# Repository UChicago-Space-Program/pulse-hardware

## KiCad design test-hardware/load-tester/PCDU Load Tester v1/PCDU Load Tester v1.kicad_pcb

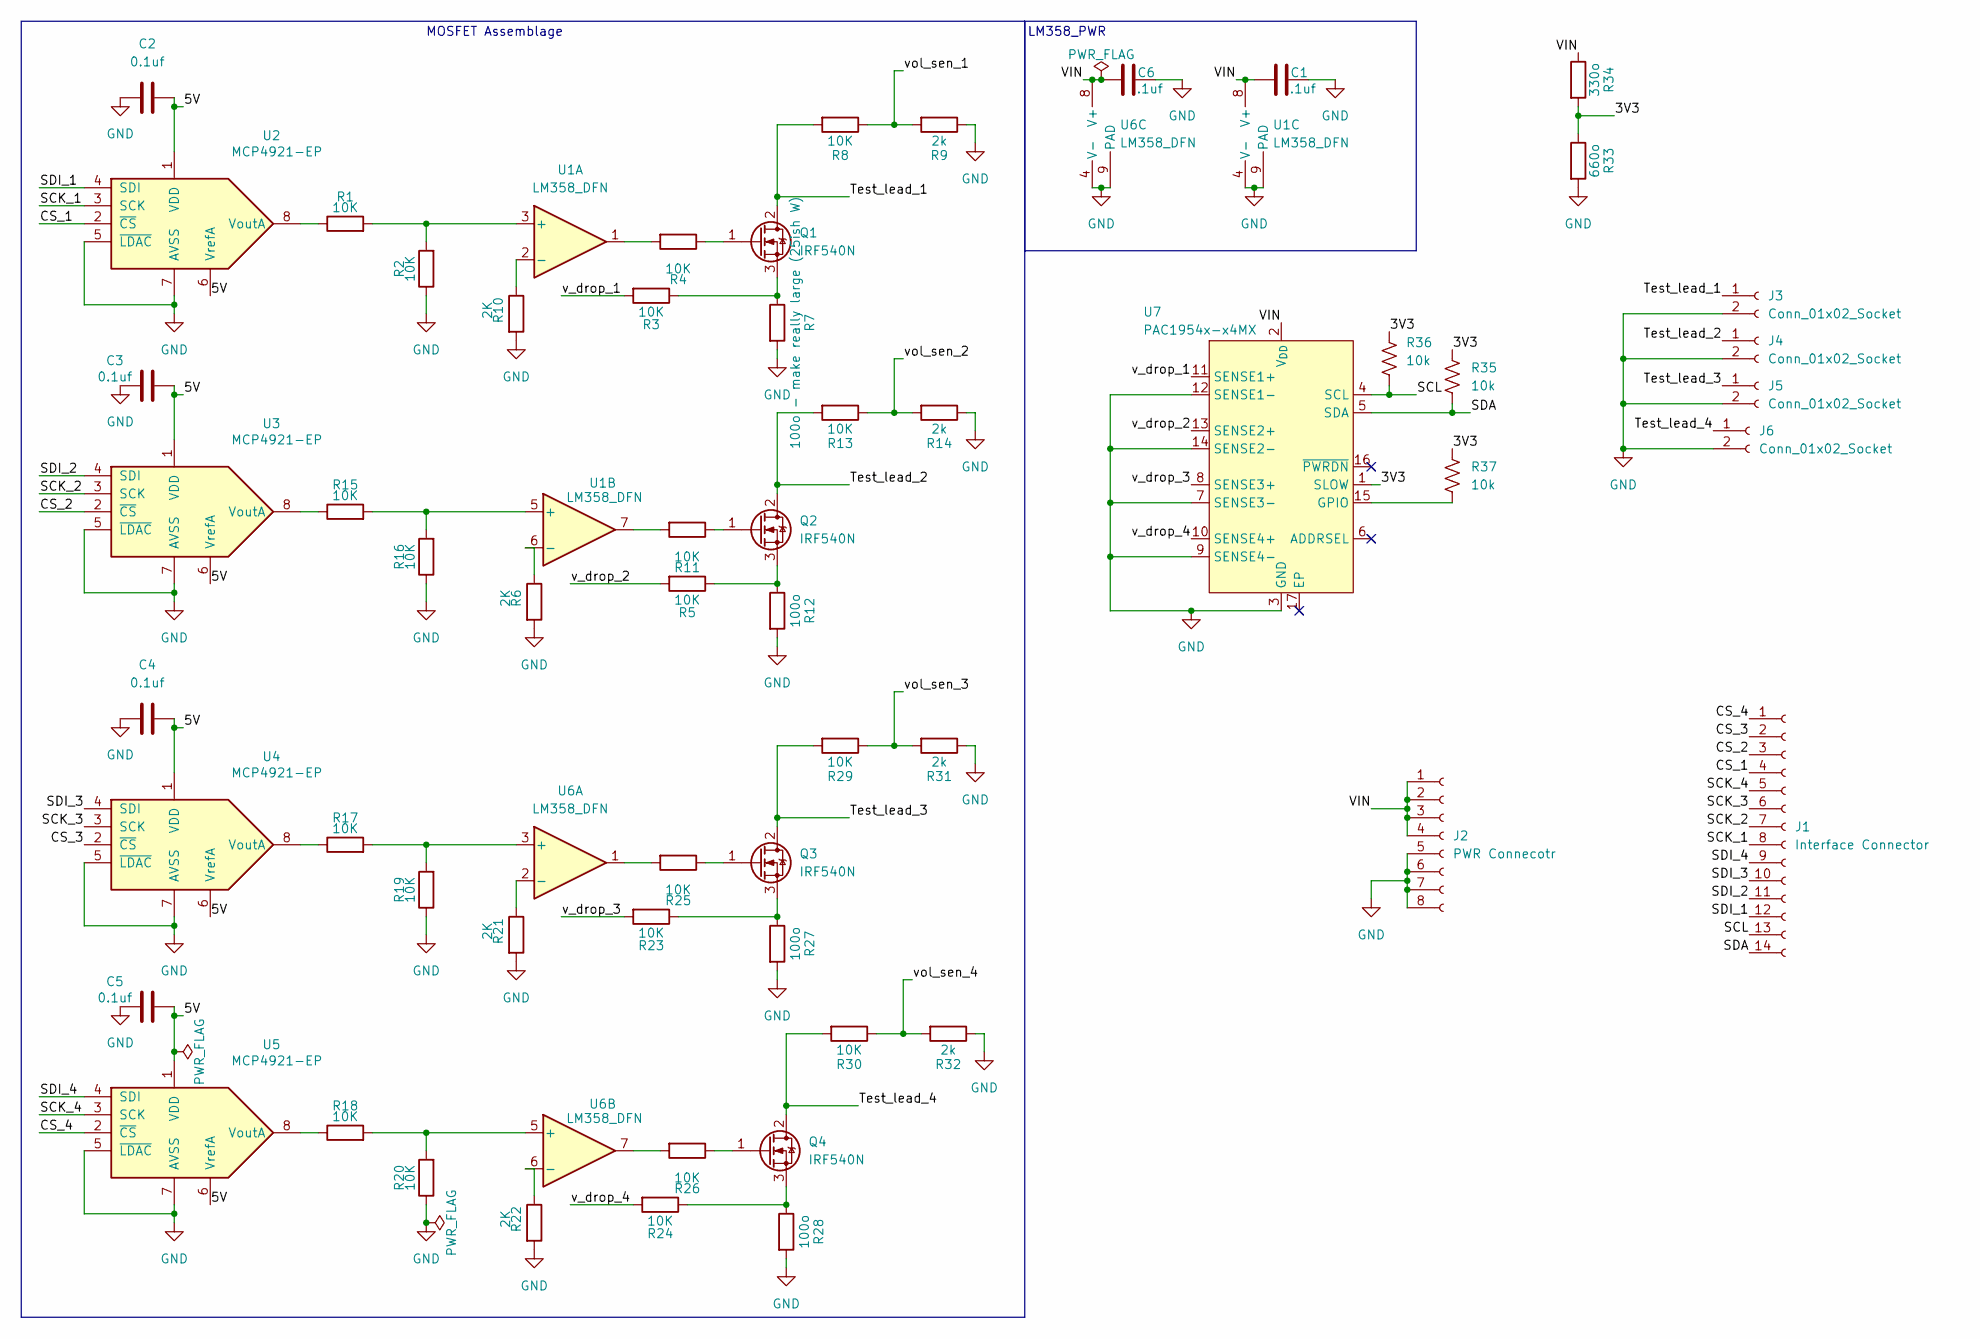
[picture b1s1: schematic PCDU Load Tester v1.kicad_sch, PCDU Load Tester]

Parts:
C1, C6: .1uf; C_0805_2012Metric
C2, C3, C4, C5: 0.1uf; C_0805_2012Metric
J1: Interface Connector; PinHeader_2x07_P2.54mm_Horizontal
J2: PWR Connecotr; PinHeader_2x04_P2.54mm_Horizontal
J3, J4, J5, J6: Conn_01x02_Socket; PinHeader_1x02_P2.54mm_Horizontal
Q1, Q2, Q3, Q4: IRF540N; TO-220-3_Vertical
R1, R2, R3, R4, R5, R8, R11, R13, R15, R16, R17, R18, R19, R20, R23, R24, R25, R26, R29, R30: 10K; R_0815_2038Metric
R6, R10, R21, R22: 2K; R_0815_2038Metric
R7: 100o - make really large (25ish W); R_0815_2038Metric
R9, R14, R31, R32: 2k; R_0815_2038Metric
R12, R27, R28: 100o; R_0815_2038Metric
R33: 660o; R_0815_2038Metric
R34: 330o; R_0815_2038Metric
R35, R36, R37: 10k; R_0815_2038Metric
U1, U6: LM358_DFN; DFN-8-1EP_2x2mm_P0.5mm_EP1.05x1.75mm
U2, U3, U4, U5: MCP4921-EP; DIP-8_W7.62mm
U7: PAC1954x-x4MX; VQFN-16-1EP_3x3mm_P0.5mm_EP1.1x1.1mm

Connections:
/3V3: R33.1, R34.2, R35.1, R36.1, R37.1, U7.1 (SLOW)
/5V: C2.1, C3.1, C4.1, C5.1, U2.1 (VDD), U2.6 (VrefA), U3.1 (VDD), U3.6 (VrefA), U4.1 (VDD), U4.6 (VrefA), U5.1 (VDD), U5.6 (VrefA)
/CS_1: J1.4, U2.2 (~CS)
/CS_2: J1.3, U3.2 (~CS)
/CS_3: J1.2, U4.2 (~CS)
/CS_4: J1.1, U5.2 (~CS)
/SCK_1: J1.8, U2.3 (SCK)
/SCK_2: J1.7, U3.3 (SCK)
/SCK_3: J1.6, U4.3 (SCK)
/SCK_4: J1.5, U5.3 (SCK)
/SCL: J1.13, R36.2, U7.4 (SCL)
/SDA: J1.14, R35.2, U7.5 (SDA)
/SDI_1: J1.12, U2.4 (SDI)
/SDI_2: J1.11, U3.4 (SDI)
/SDI_3: J1.10, U4.4 (SDI)
/SDI_4: J1.9, U5.4 (SDI)
/Test_lead_1: J3.1, Q1.2 (D), R8.2
/Test_lead_2: J4.1, Q2.2 (D), R13.2
/Test_lead_3: J5.1, Q3.2 (D), R29.2
/Test_lead_4: J6.1, Q4.2 (D), R30.2
/VIN: C1.1, C6.1, J2.1, J2.2, J2.3, J2.4, R34.1, U1.8 (V+), U6.8 (V+), U7.2 (V_{DD})
/v_drop_1: R3.2, U7.11 (SENSE1+)
/v_drop_2: R5.2, U7.13 (SENSE2+)
/v_drop_3: R23.2, U7.8 (SENSE3+)
/v_drop_4: R24.2, U7.10 (SENSE4+)
/vol_sen_1: R8.1, R9.2
/vol_sen_2: R13.1, R14.2
/vol_sen_3: R29.1, R31.2
/vol_sen_4: R30.1, R32.2
GND: C1.2, C2.2, C3.2, C4.2, C5.2, C6.2, J2.5, J2.6, J2.7, J2.8, J3.2, J4.2, J5.2, J6.2, R2.1, R6.2, R7.2, R9.1, R10.2, R12.2, R14.1, R16.1, R19.1, R20.1, R21.2, R22.2, R27.2, R28.2, R31.1, R32.1, R33.2, U1.4 (V-), U1.9 (PAD), U2.5 (~LDAC), U2.7 (AVSS), U3.5 (~LDAC), U3.7 (AVSS), U4.5 (~LDAC), U4.7 (AVSS), U5.5 (~LDAC), U5.7 (AVSS), U6.4 (V-), U6.9 (PAD), U7.3 (GND), U7.7 (SENSE3-), U7.9 (SENSE4-), U7.12 (SENSE1-), U7.14 (SENSE2-)
unnamed: Q1.1 (G), R4.1
unnamed: Q1.3 (S), R3.1, R7.1
unnamed: Q2.1 (G), R11.1
unnamed: Q2.3 (S), R5.1, R12.1
unnamed: Q3.1 (G), R25.1
unnamed: Q3.3 (S), R23.1, R27.1
unnamed: Q4.1 (G), R26.1
unnamed: Q4.3 (S), R24.1, R28.1
unnamed: R4.2, U1.1
unnamed: R11.2, U1.7
unnamed: R25.2, U6.1
unnamed: R26.2, U6.7
unnamed: R1.2, R2.2, U1.3 (+)
unnamed: R10.1, U1.2 (-)
unnamed: R15.2, R16.2, U1.5 (+)
unnamed: R6.1, U1.6 (-)
unnamed: R1.1, U2.8 (VoutA)
unnamed: R15.1, U3.8 (VoutA)
unnamed: R17.1, U4.8 (VoutA)
unnamed: R18.1, U5.8 (VoutA)
unnamed: R17.2, R19.2, U6.3 (+)
unnamed: R21.1, U6.2 (-)
unnamed: R18.2, R20.2, U6.5 (+)
unnamed: R22.1, U6.6 (-)
unnamed: R37.2, U7.15 (GPIO)

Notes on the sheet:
LM358_PWR
MOSFET Assemblage

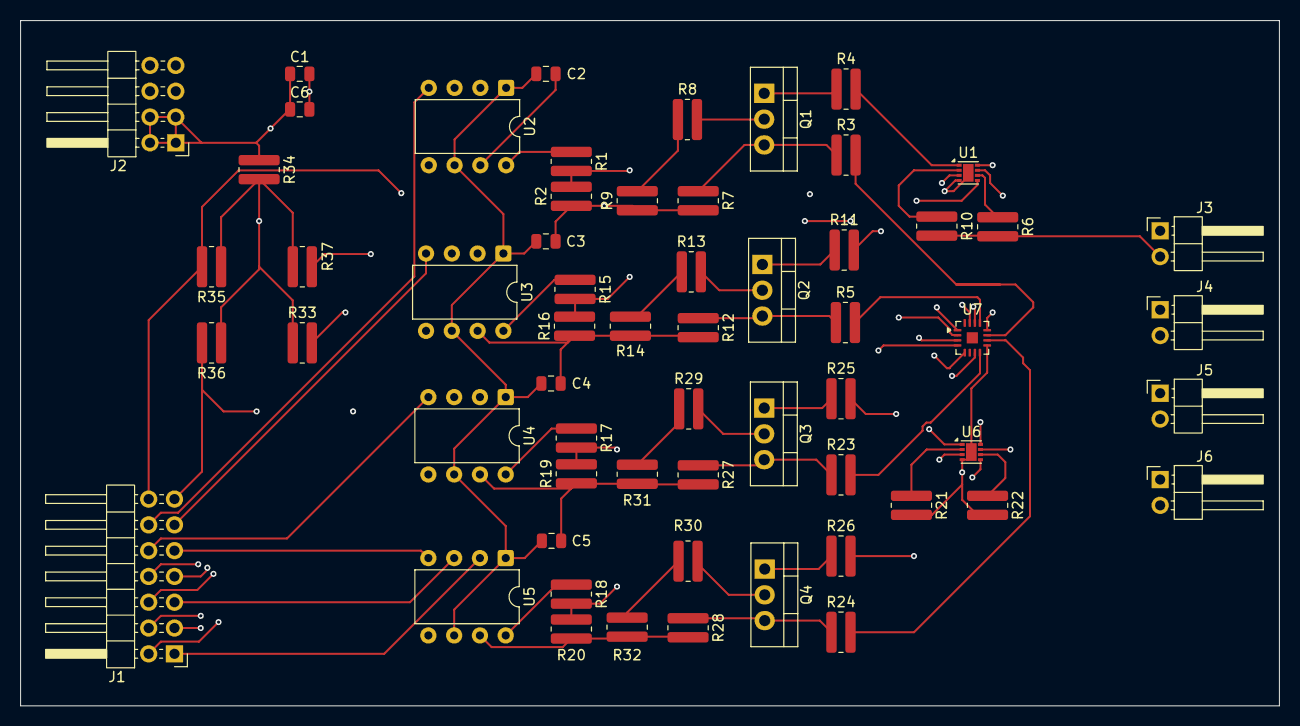
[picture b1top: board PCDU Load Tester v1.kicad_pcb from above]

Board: 4 copper layers, 124.0 x 67.5 mm, 60 parts (0 on the bottom side), 55 nets.

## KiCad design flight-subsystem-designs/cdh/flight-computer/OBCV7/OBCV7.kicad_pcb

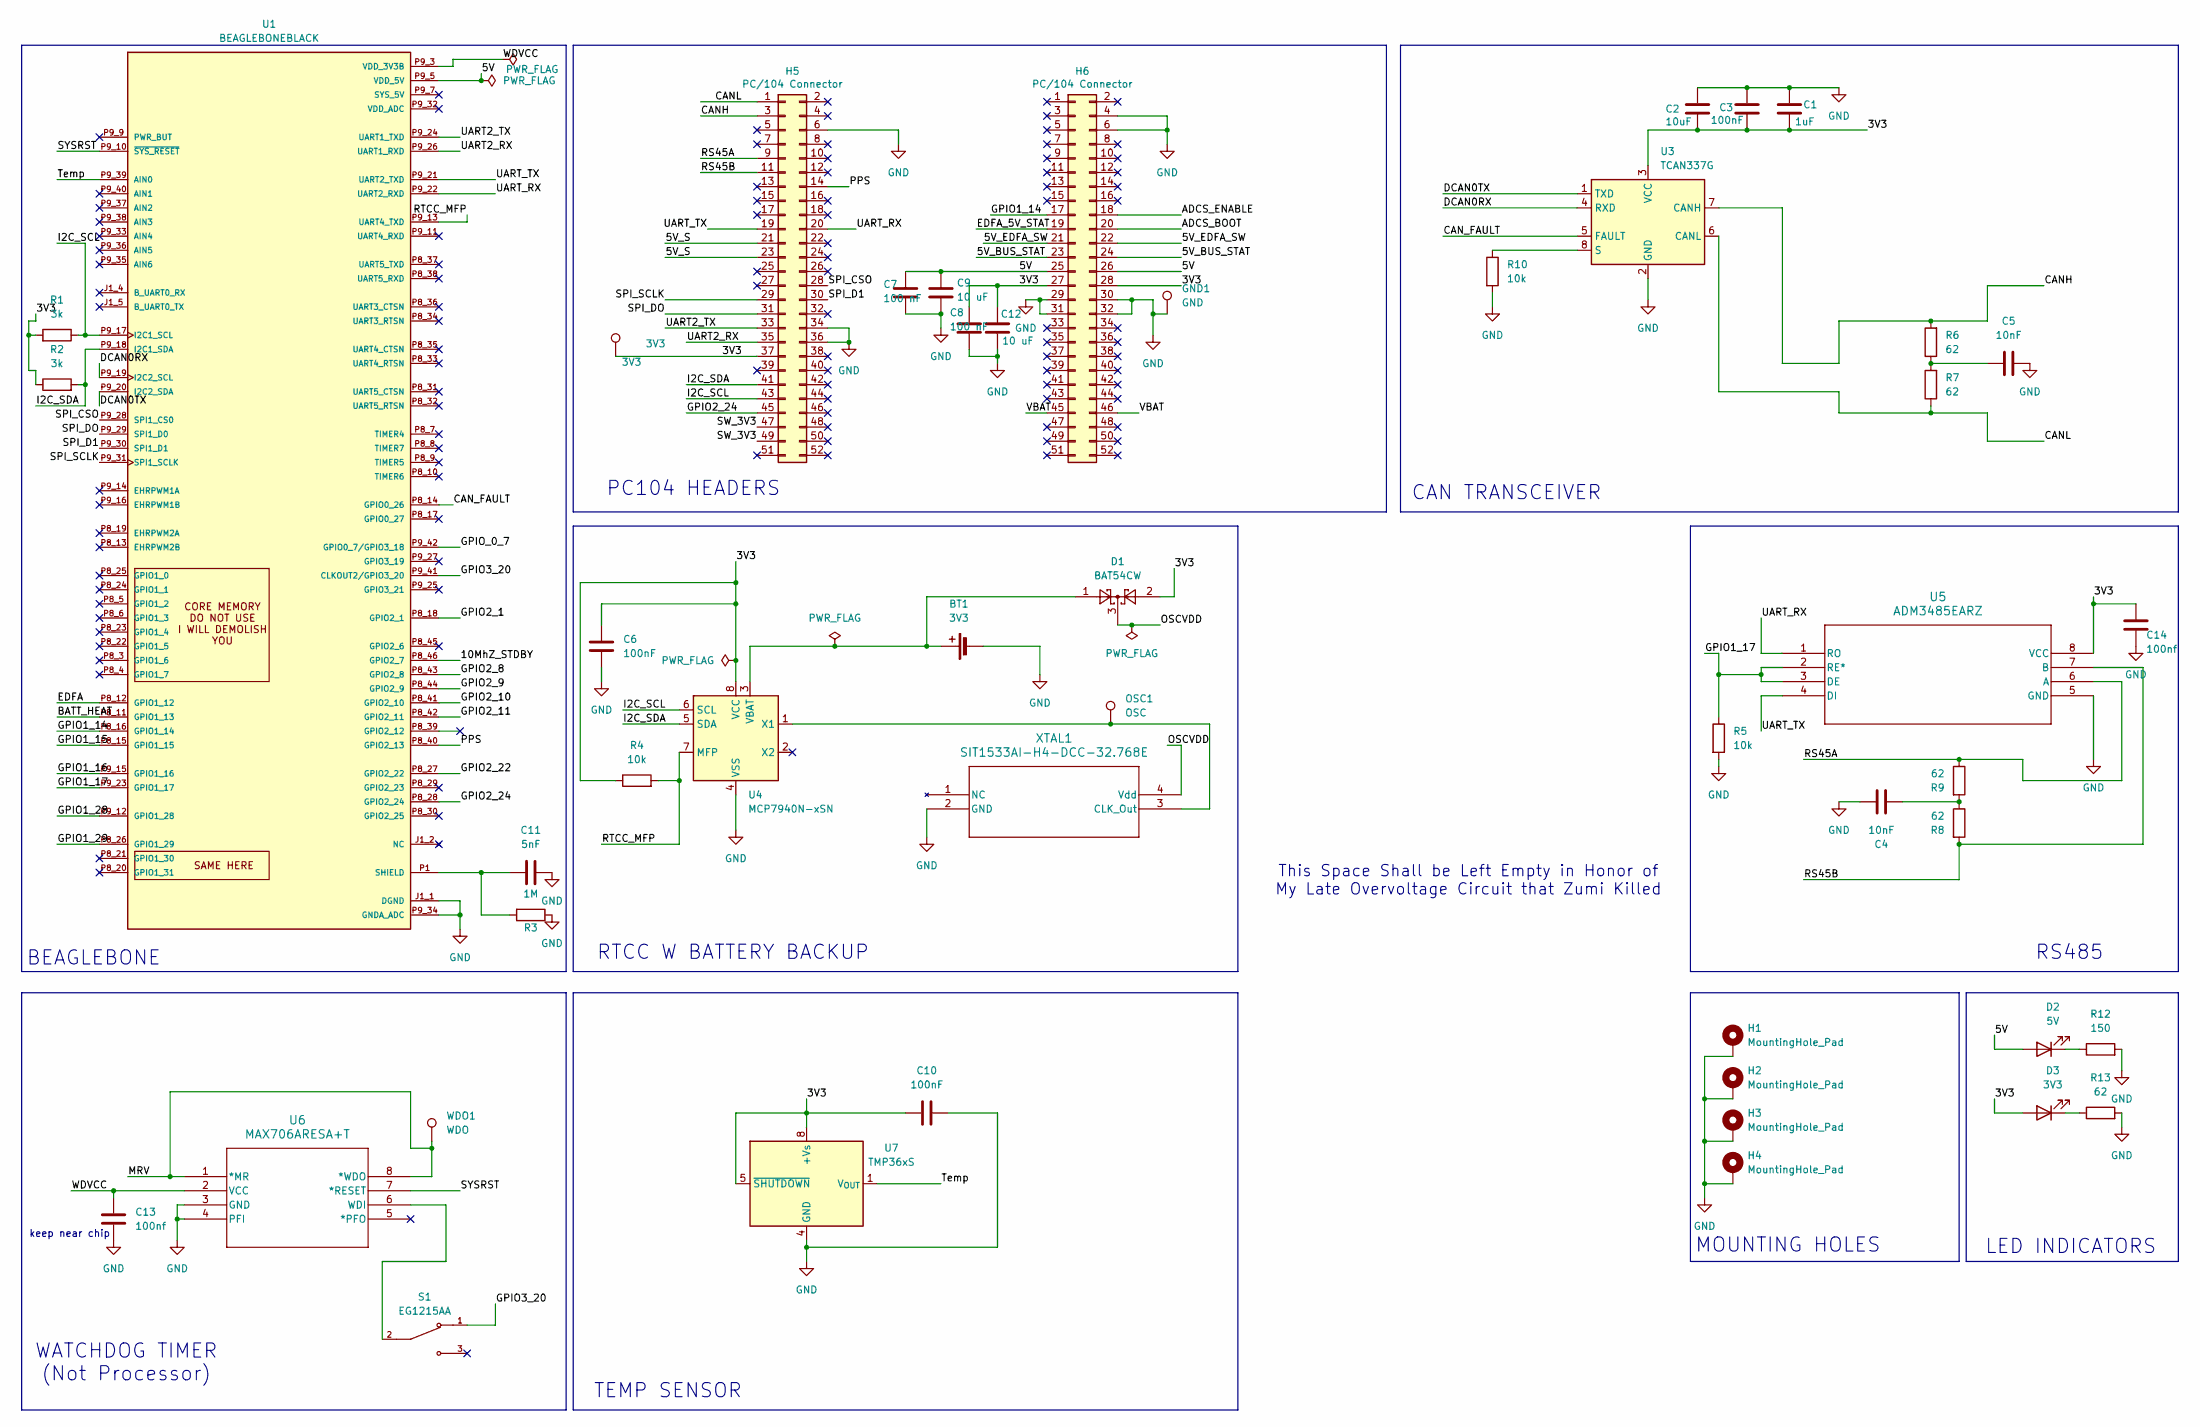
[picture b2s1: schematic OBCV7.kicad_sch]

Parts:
3V3: 3V3; TestPoint_THTPad_D3.0mm_Drill1.5mm
BT1: 3V3; BatteryHolder_Keystone_106_1x20mm
C1: 1uF; C_0805_2012Metric_Pad1.18x1.45mm_HandSolder
C2: 10uF; C_0805_2012Metric_Pad1.18x1.45mm_HandSolder
C3, C6, C10: 100nF; C_0805_2012Metric_Pad1.18x1.45mm_HandSolder
C4, C5: 10nF; C_0805_2012Metric_Pad1.18x1.45mm_HandSolder
C7, C8: 100 nF; C_0805_2012Metric_Pad1.18x1.45mm_HandSolder
C9, C12: 10 uF; C_0805_2012Metric_Pad1.18x1.45mm_HandSolder
C11: 5nF; C_0805_2012Metric_Pad1.18x1.45mm_HandSolder
C13, C14: 100nf; C_0805_2012Metric_Pad1.18x1.45mm_HandSolder
D1: BAT54CW; SOT-323_SC-70
D2: 5V; LED_0805_2012Metric
D3: 3V3; LED_0805_2012Metric
GND1: GND; TestPoint_THTPad_D3.0mm_Drill1.5mm
H1, H2, H3, H4: MountingHole_Pad; MountingHole_3.2mm_M3_Pad_TopBottom
H5, H6: PC/104 Connector; PinSocket_2x26_P2.54mm_Vertical
OSC1: OSC; TestPoint_THTPad_D3.0mm_Drill1.5mm
R1, R2: 3k; R_0805_2012Metric_Pad1.20x1.40mm_HandSolder
R3: 1M; R_0805_2012Metric_Pad1.20x1.40mm_HandSolder
R4, R5, R10: 10k; R_0805_2012Metric_Pad1.20x1.40mm_HandSolder
R6, R7, R8, R9: 62; R_0805_2012Metric_Pad1.20x1.40mm_HandSolder
R12: 150; LED_0805_2012Metric
R13: 62; LED_0805_2012Metric
S1: EG1215AA; SW_EG1215AA; PARTREV A
U1: BEAGLEBONEBLACK; MODULE_BEAGLEBONEBLACK; PARTREV C
U3: TCAN337G; TCAN337GD
U4: MCP7940N-xSN; SOIC8-N_MC_MCH
U5: ADM3485EARZ; R_8_ADI
U6: MAX706ARESA+T; 21-0041B_8_MXM
U7: TMP36xS; SOIC-8_3.9x4.9mm_P1.27mm
WDO1: WDO; TestPoint_THTPad_D3.0mm_Drill1.5mm
XTAL1: SIT1533AI-H4-DCC-32.768E; XTAL4_SiT1533_SIT

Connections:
/3V3: 3V3.1, C1.1, C2.2, C3.1, C6.1, C8.1, C10.1, C12.1, C14.2, D1.2, D3.2 (A), H5.37, H6.27, H6.28, R1.2, R2.1, R4.1, U3.3 (VCC), U4.8 (VCC), U5.8 (VCC), U7.5 (~SHUTDOWN), U7.8 (+Vs)
/5V_BUS_STAT: H6.23, H6.24
/5V_EDFA_SW: H6.21, H6.22
/5V_S: H5.21, H5.23
/10MhZ_STDBY: U1.P8_46 (GPIO2_7)
/ADCS_BOOT: H6.20
/ADCS_ENABLE: H6.18
/BATT_HEAT: U1.P8_11 (GPIO1_13)
/CANH: H5.3, R6.2, U3.7 (CANH)
/CANL: H5.1, R7.1, U3.6 (CANL)
/CAN_FAULT: U1.P8_14 (GPIO0_26), U3.5 (FAULT)
/DCAN0RX: U1.P9_19 (I2C2_SCL), U3.4 (RXD)
/DCAN0TX: U1.P9_20 (I2C2_SDA), U3.1 (TXD)
/EDFA: U1.P8_12 (GPIO1_12)
/EDFA_5V_STAT: H6.19
/GPIO1_14: H6.17, U1.P8_16 (GPIO1_14)
/GPIO1_15: U1.P8_15 (GPIO1_15)
/GPIO1_16: U1.P9_15 (GPIO1_16)
/GPIO1_17: R5.1, U1.P9_23 (GPIO1_17), U5.2 (RE*), U5.3 (DE)
/GPIO1_28: U1.P9_12 (GPIO1_28)
/GPIO1_29: U1.P8_26 (GPIO1_29)
/GPIO2_1: U1.P8_18 (GPIO2_1)
/GPIO2_8: U1.P8_43 (GPIO2_8)
/GPIO2_9: U1.P8_44 (GPIO2_9)
/GPIO2_10: U1.P8_41 (GPIO2_10)
/GPIO2_11: U1.P8_42 (GPIO2_11)
/GPIO2_22: U1.P8_27 (GPIO2_22)
/GPIO2_24: H5.45, U1.P8_28 (GPIO2_24)
/GPIO3_20: S1.1, U1.P9_41 (CLKOUT2/GPIO3_20)
/GPIO_0_7: U1.P9_42 (GPIO0_7/GPIO3_18)
/I2C_SCL: H5.43, R1.1, U1.P9_17 (I2C1_SCL), U4.6 (SCL)
/I2C_SDA: H5.41, R2.2, U1.P9_18 (I2C1_SDA), U4.5 (SDA)
/MRV: U6.1 (*MR), U6.8 (*WDO), WDO1.1
/OSCVDD: D1.3, XTAL1.4 (Vdd)
/PPS: H5.14, U1.P8_40 (GPIO2_13)
/RS45A: H5.9, R9.1, U5.6 (A)
/RS45B: H5.11, R8.2, U5.7 (B)
/RTCC_MFP: R4.2, U1.P9_13 (UART4_TXD), U4.7 (MFP)
/SPI_CSO: H5.28, U1.P9_28 (SPI1_CS0)
/SPI_D1: H5.30, U1.P9_30 (SPI1_D1)
/SPI_DO: H5.31, U1.P9_29 (SPI1_D0)
/SPI_SCLK: H5.29, U1.P9_31 (SPI1_SCLK)
/SW_3V3: H5.47, H5.49
/SYSRST: U1.P9_10 (~SYS_RESET), U6.7 (*RESET)
/Temp: U1.P9_39 (AIN0), U7.1 (V_{OUT})
/UART2_RX: H5.35, U1.P9_26 (UART1_RXD)
/UART2_TX: H5.33, U1.P9_24 (UART1_TXD)
/UART_RX: H5.20, U1.P9_22 (UART2_RXD), U5.1 (RO)
/UART_TX: H5.19, U1.P9_21 (UART2_TXD), U5.4 (DI)
/VBAT: H6.45, H6.46
GND: BT1.2 (-), C1.2, C2.1, C3.2, C4.2, C5.2, C6.2, C7.2, C8.2, C9.2, C10.2, C11.2, C12.2, C13.1, C14.1, GND1.1, H1.1, H2.1, H3.1, H4.1, H5.6, H5.34, H5.36, H6.4, H6.6, H6.29, H6.30, H6.31, H6.32, R3.1, R5.2, R10.2, R12.2, R13.2, U1.J1_1 (DGND), U1.P8_1 (DGND), U1.P8_2 (DGND), U1.P9_1 (DGND), U1.P9_2 (DGND), U1.P9_34 (GNDA_ADC), U1.P9_43 (DGND), U1.P9_44 (DGND), U1.P9_45 (DGND), U1.P9_46 (DGND), U3.2 (GND), U4.4 (VSS), U5.5 (GND), U6.3 (GND), U6.4 (PFI), U7.4 (GND), XTAL1.2 (GND)
unnamed: BT1.1 (+), D1.1, U4.3 (VBAT)
unnamed: C4.1, R8.1, R9.2
unnamed: C5.1, R6.1, R7.2
unnamed: C11.1, R3.2, U1.P1 (SHIELD), U1.P2 (SHIELD), U1.P3 (SHIELD), U1.P4 (SHIELD)
unnamed: D2.1 (K), R12.1
unnamed: D3.1 (K), R13.1
unnamed: R10.1, U3.8 (S)
unnamed: OSC1.1, U4.1 (X1), XTAL1.3 (CLK_Out)
unnamed: S1.2, U6.6 (WDI)
VDD_3V3B: C13.2, U1.P9_3 (VDD_3V3B), U1.P9_4 (VDD_3V3B), U6.2 (VCC)
VDD_5V: C7.1, C9.1, D2.2 (A), H6.25, H6.26, U1.P9_5 (VDD_5V), U1.P9_6 (VDD_5V)

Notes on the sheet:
RS485
TEMP SENSOR
This Space Shall be Left Empty in Honor of My Late Overvoltage Circuit that Zumi Killed
PC104 HEADERS
LED INDICATORS
CAN TRANSCEIVER
WATCHDOG TIMER (Not Processor)
RTCC W BATTERY BACKUP
MOUNTING HOLES
keep near chip
BEAGLEBONE

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
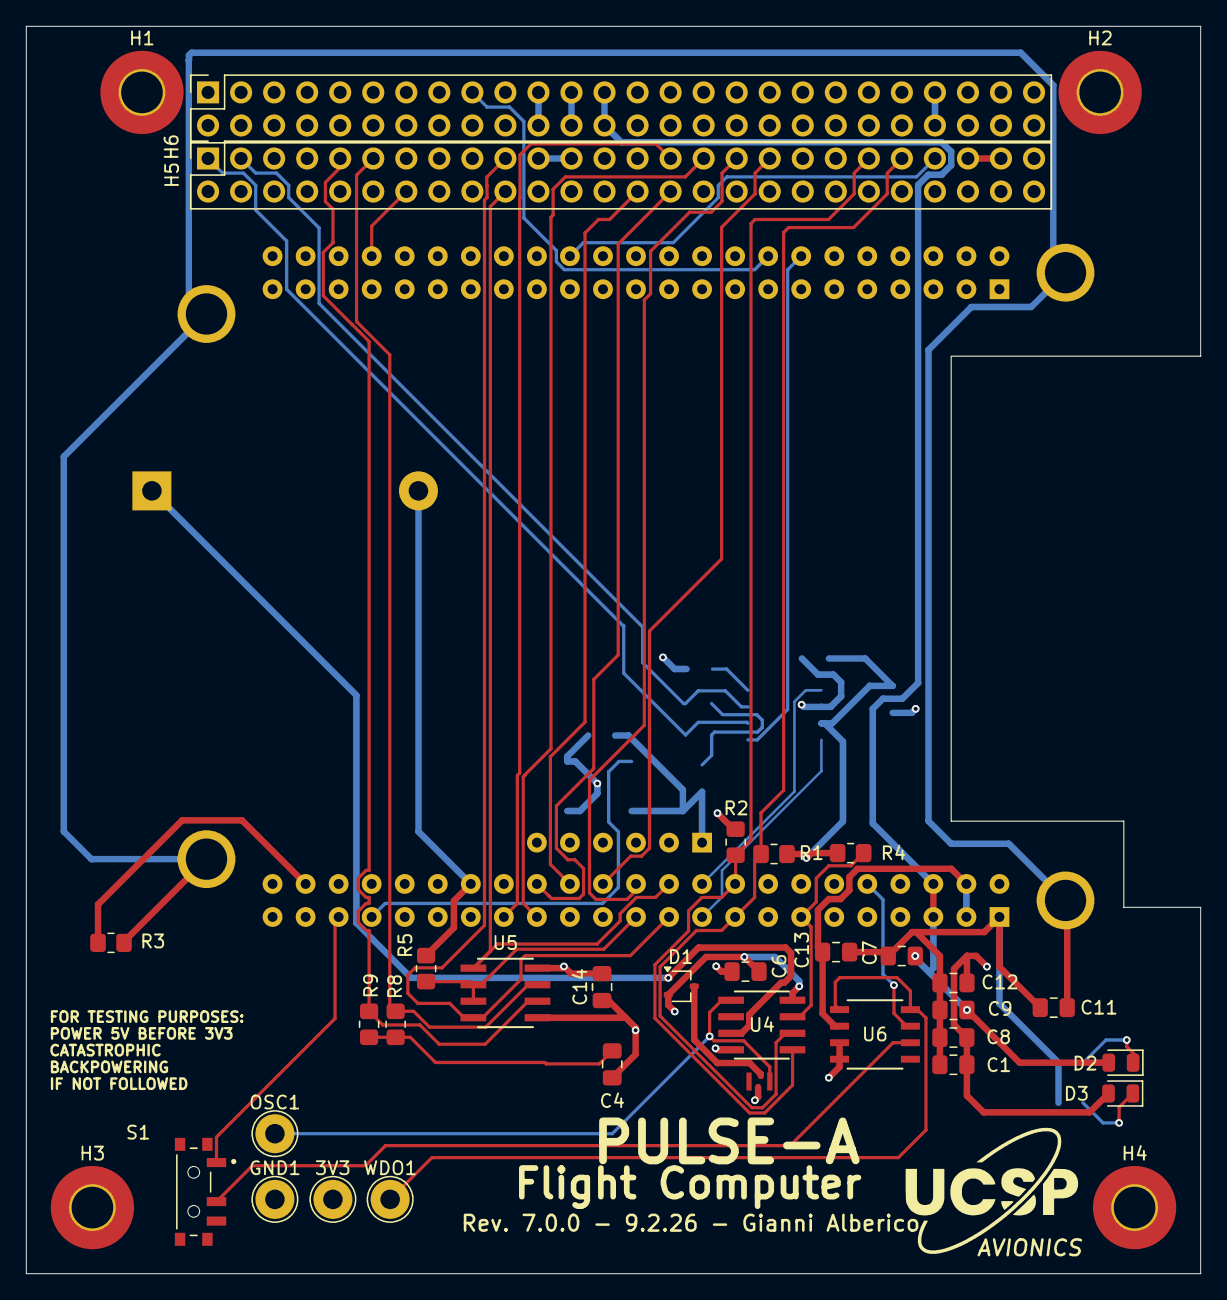
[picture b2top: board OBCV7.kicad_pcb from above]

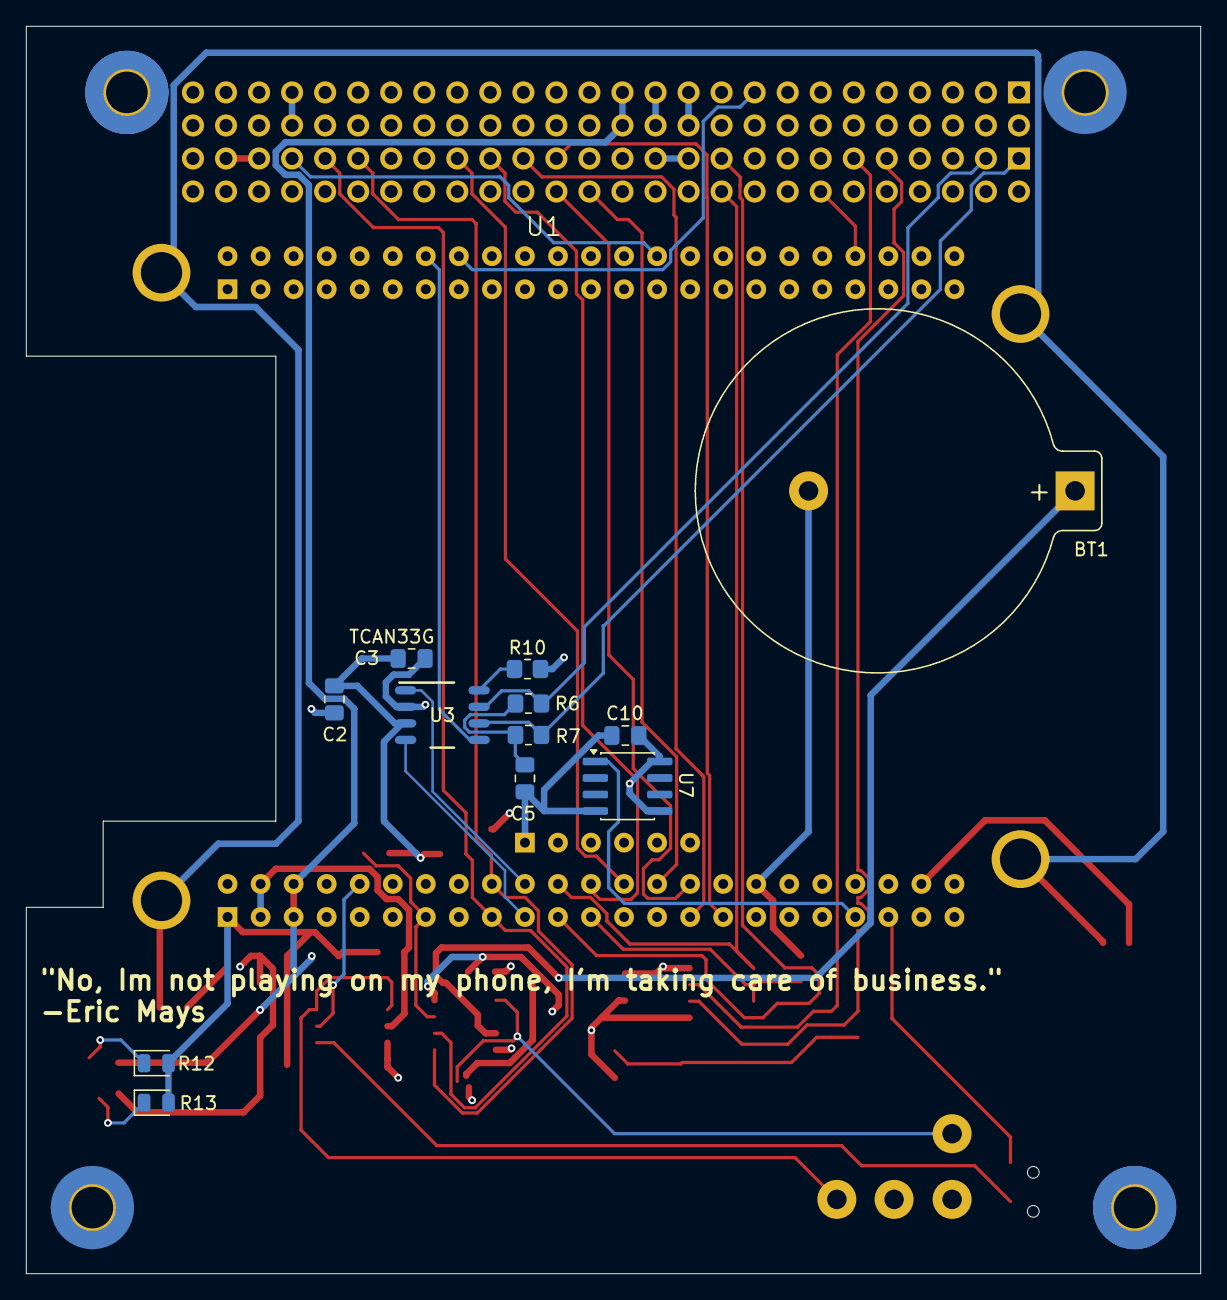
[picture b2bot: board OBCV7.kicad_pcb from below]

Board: 4 copper layers, 90.3 x 95.9 mm, 48 parts (13 on the bottom side), 45 nets.

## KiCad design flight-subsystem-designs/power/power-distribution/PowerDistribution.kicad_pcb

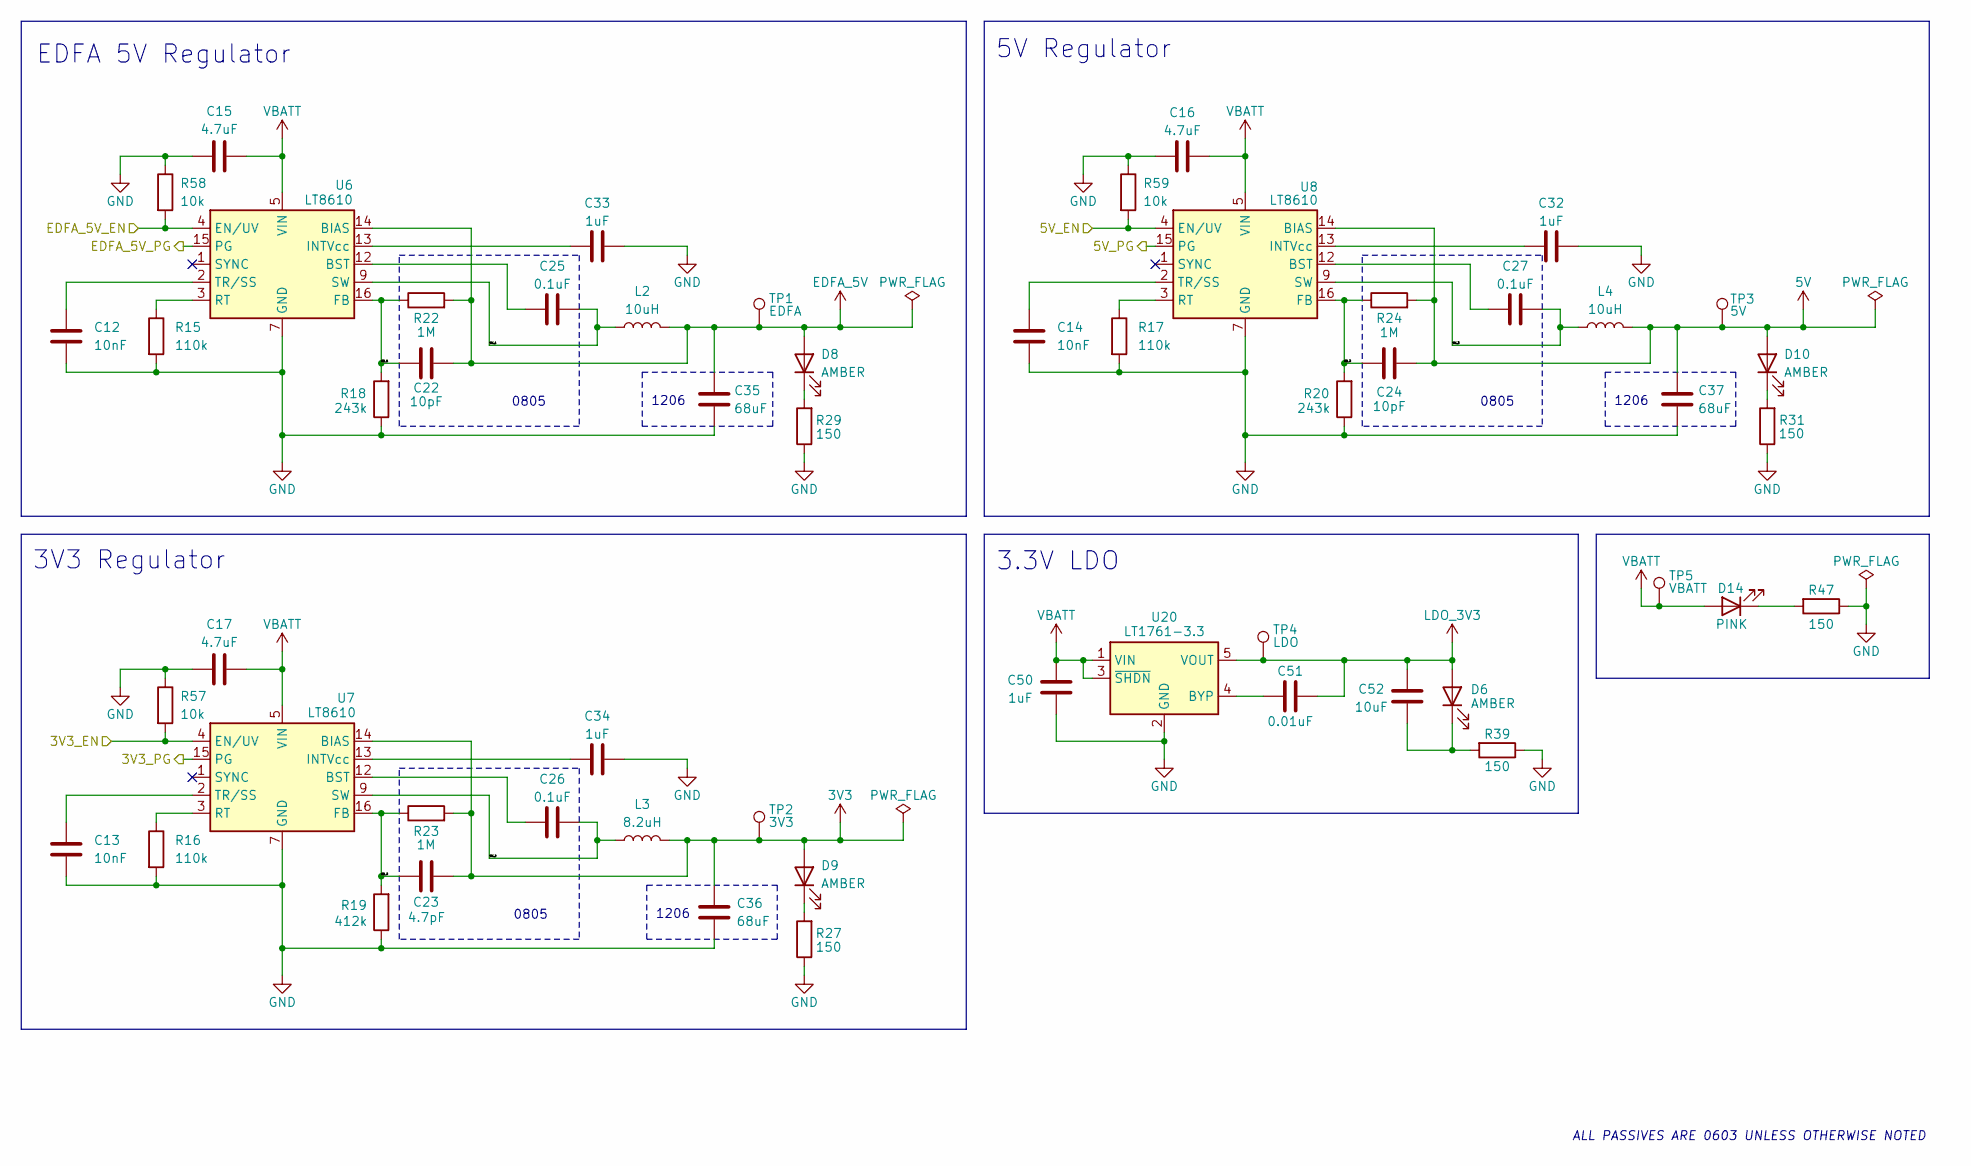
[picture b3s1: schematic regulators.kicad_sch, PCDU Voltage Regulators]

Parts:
C12, C13, C14: 10nF; C_0603_1608Metric
C15, C16, C17: 4.7uF; C_0603_1608Metric
C22, C24: 10pF; C_0805_2012Metric
C23: 4.7pF; C_0805_2012Metric
C25, C26, C27: 0.1uF; C_0805_2012Metric
C32, C33, C34, C50: 1uF; C_0603_1608Metric
C35, C36, C37: 68uF; C_1206_3216Metric
C51: 0.01uF; C_0603_1608Metric
C52: 10uF; C_0603_1608Metric
D6, D8, D9, D10: AMBER; LED_0603_1608Metric
D14: PINK; LED_0603_1608Metric
L2, L4: 10uH; L_Coilcraft_XxL4040
L3: 8.2uH; L_Coilcraft_XxL4040
R15, R16, R17: 110k; R_0603_1608Metric
R18, R20: 243k; R_0805_2012Metric
R19: 412k; R_0805_2012Metric
R22, R23, R24: 1M; R_0805_2012Metric
R27, R29, R31, R39, R47: 150; R_0603_1608Metric
R57, R58, R59: 10k; R_0603_1608Metric
TP1: EDFA; TestPoint_Keystone_5000-5004_Miniature
TP2: 3V3; TestPoint_Keystone_5000-5004_Miniature
TP3: 5V; TestPoint_Keystone_5000-5004_Miniature
TP4: LDO; TestPoint_Keystone_5000-5004_Miniature
TP5: VBATT; TestPoint_Keystone_5000-5004_Miniature
U6, U7, U8: LT8610; MSOP-16-1EP_3x4.039mm_P0.5mm_EP1.651x2.845mm_ThermalVias
U20: LT1761-3.3; TSOT-23-5

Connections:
3V3: C23.2, C36.2, D9.2 (A), L3.2, R23.2, TP2.1, U7.14 (BIAS); also elsewhere on the board
5V: C24.2, C37.2, D10.2 (A), L4.2, R24.2, TP3.1, U8.14 (BIAS); also elsewhere on the board
/Control/3V3_EN: R57.2, U7.4 (EN/UV); also elsewhere on the board
/Control/3V3_PG: U7.15 (PG); also elsewhere on the board
/Control/5V_EN: R59.2, U8.4 (EN/UV); also elsewhere on the board
/Control/5V_PG: U8.15 (PG); also elsewhere on the board
/Control/EDFA_5V_EN: R58.2, U6.4 (EN/UV); also elsewhere on the board
/Control/EDFA_5V_PG: U6.15 (PG); also elsewhere on the board
/Regulators/FB_1: C22.1, R18.2, R22.1, U6.16 (FB)
/Regulators/FB_2: C23.1, R19.2, R23.1, U7.16 (FB)
/Regulators/FB_3: C24.1, R20.2, R24.1, U8.16 (FB)
/Regulators/SW_1: C25.2, L2.1, U6.9 (SW), U6.10 (SW), U6.11 (SW)
/Regulators/SW_2: C26.2, L3.1, U7.9 (SW), U7.10 (SW), U7.11 (SW)
/Regulators/SW_3: C27.2, L4.1, U8.9 (SW), U8.10 (SW), U8.11 (SW)
EDFA_5V: C22.2, C35.2, D8.2 (A), L2.2, R22.2, TP1.1, U6.14 (BIAS); also elsewhere on the board
GND: C12.1, C13.1, C14.1, C15.1, C16.2, C17.1, C32.2, C33.2, C34.2, C35.1, C36.1, C37.1, C50.1, R15.2, R16.2, R17.2, R18.1, R19.1, R20.1, R27.1, R29.1, R31.1, R39.1, R47.1, R57.1, R58.1, R59.1, U6.7 (GND), U6.8 (GND), U6.17 (GND), U7.7 (GND), U7.8 (GND), U7.17 (GND), U8.7 (GND), U8.8 (GND), U8.17 (GND), U20.2 (GND); also elsewhere on the board
LDO_3V3: C51.1, C52.2, D6.2 (A), TP4.1, U20.5 (VOUT); also elsewhere on the board
unnamed: C52.1, D6.1 (K), R39.2
unnamed: D8.1 (K), R29.2
unnamed: D9.1 (K), R27.2
unnamed: D10.1 (K), R31.2
unnamed: D14.1 (K), R47.2
unnamed: C25.1, U6.12 (BST)
unnamed: C33.1, U6.13 (INTVcc)
unnamed: R15.1, U6.3 (RT)
unnamed: C12.2, U6.2 (TR/SS)
unnamed: C26.1, U7.12 (BST)
unnamed: C34.1, U7.13 (INTVcc)
unnamed: R16.1, U7.3 (RT)
unnamed: C13.2, U7.2 (TR/SS)
unnamed: C27.1, U8.12 (BST)
unnamed: C32.1, U8.13 (INTVcc)
unnamed: R17.1, U8.3 (RT)
unnamed: C14.2, U8.2 (TR/SS)
unnamed: C51.2, U20.4 (BYP)
VBATT: C15.2, C16.1, C17.2, C50.2, D14.2 (A), TP5.1, U6.5 (VIN), U6.6 (VIN), U7.5 (VIN), U7.6 (VIN), U8.5 (VIN), U8.6 (VIN), U20.1 (VIN), U20.3 (~SHDN); also elsewhere on the board

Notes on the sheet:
5V Regulator
EDFA 5V Regulator
1206
0805
3.3V LDO
ALL PASSIVES ARE 0603 UNLESS OTHERWISE NOTED
3V3 Regulator

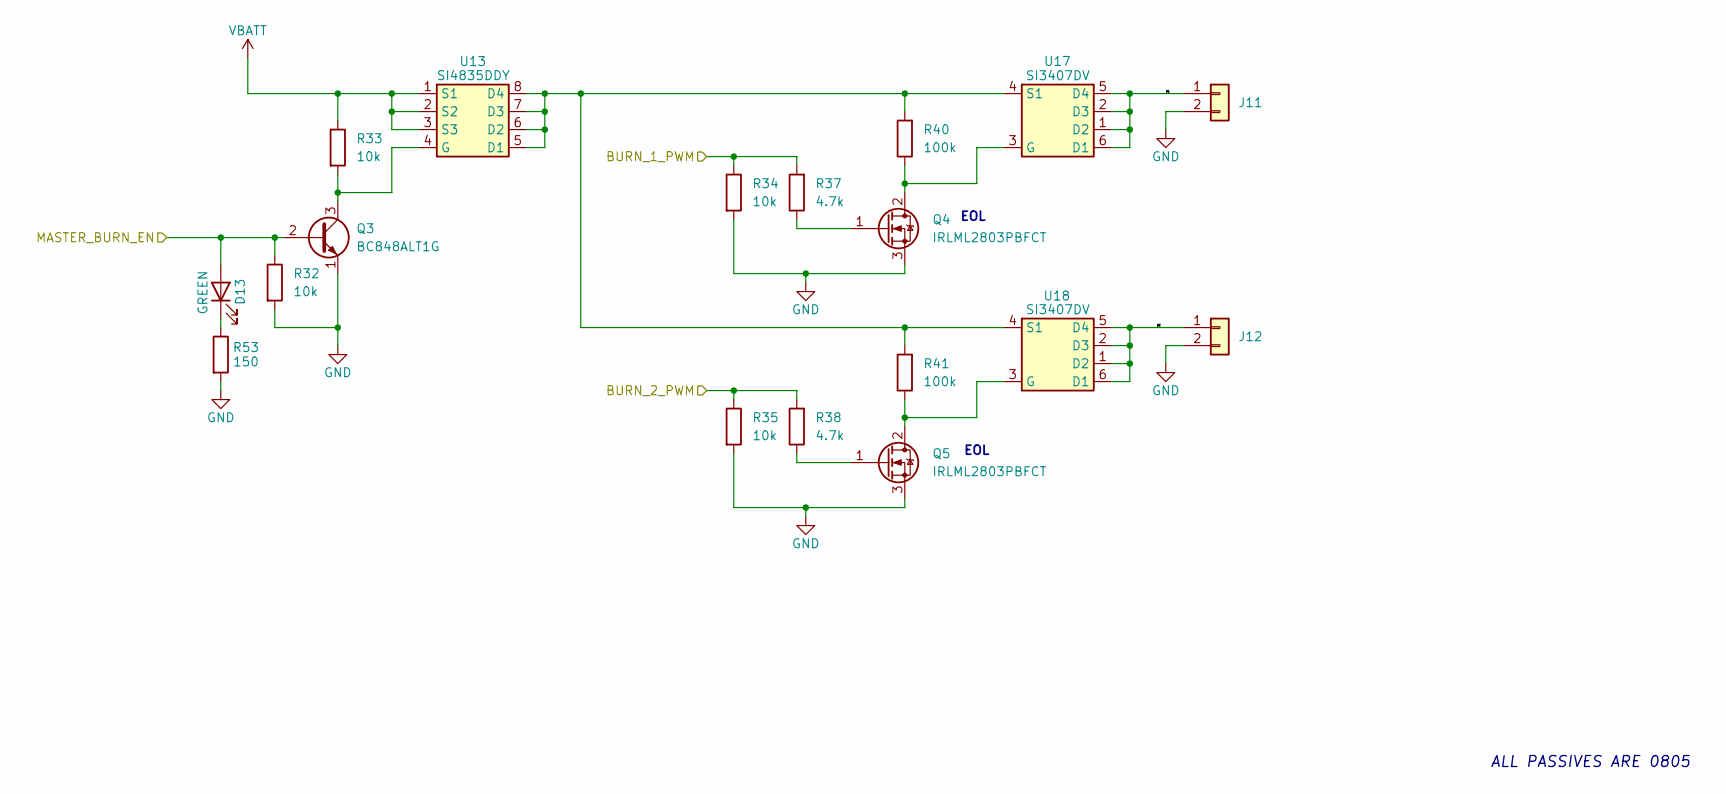
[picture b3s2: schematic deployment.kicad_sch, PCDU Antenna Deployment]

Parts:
D13: GREEN; LED_0603_1608Metric
J11, J12: Conn_01x02; Molex_PicoBlade_53047-0210_1x02_P1.25mm_Vertical
Q3: BC848ALT1G; SOT-23-3
Q4, Q5: IRLML2803PBFCT; SOT-23-3
R32, R33, R34, R35: 10k; R_0805_2012Metric
R37, R38: 4.7k; R_0805_2012Metric
R40, R41: 100k; R_0805_2012Metric
R53: 150; R_0603_1608Metric
U13: SI4835DDY; SOIC-8_3.9x4.9mm_P1.27mm
U17, U18: SI3407DV; TSOP-6_1.65x3.05mm_P0.95mm

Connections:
/Control/BURN_1_PWM: R34.1, R37.2; also elsewhere on the board
/Control/BURN_2_PWM: R35.1, R38.2; also elsewhere on the board
/Control/MASTER_BURN_EN: D13.2 (A), Q3.2 (B), R32.1; also elsewhere on the board
/Deployment/b1: J11.1, U17.1 (D2), U17.2 (D3), U17.5 (D4), U17.6 (D1)
/Deployment/b2: J12.1, U18.1 (D2), U18.2 (D3), U18.5 (D4), U18.6 (D1)
GND: J11.2, J12.2, Q3.1 (E), Q4.3 (S), Q5.3 (S), R32.2, R34.2, R35.2, R53.2; also elsewhere on the board
unnamed: D13.1 (K), R53.1
unnamed: Q3.3 (C), R33.2, U13.4 (G)
unnamed: Q4.2 (D), R40.1, U17.3 (G)
unnamed: Q4.1 (G), R37.1
unnamed: Q5.2 (D), R41.1, U18.3 (G)
unnamed: Q5.1 (G), R38.1
unnamed: R40.2, R41.2, U13.5 (D1), U13.6 (D2), U13.7 (D3), U13.8 (D4), U17.4 (S1), U18.4 (S1)
VBATT: R33.1, U13.1 (S1), U13.2 (S2), U13.3 (S3); also elsewhere on the board

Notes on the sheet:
EOL
ALL PASSIVES ARE 0805
